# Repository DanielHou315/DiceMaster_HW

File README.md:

# DiceMaster HW

Hardware design files for the DiceMaster project, using KiCad.

## Board Status

The current production board is **PCB v1** (`PCB/DiceMaster_Router/`), finalized
for production on 2026-04-05 (commit `4ef69b5`, "finalized pcb v1 for prod").
Gerbers and the JLCPCB BOM under `PCB/DiceMaster_Router/gerbers/` are from this
run; the manufactured boards were received around mid-April 2026.

### Known issues (PCB v1 — unverified, to be handled later)

These issues were observed on the v1 boards but **not yet root-caused**:

1. **Some JST ports could not be soldered during manufacturing.** One or more of
   the JST GH SMD connectors (`J_A1`–`J_F1`, `J_BTN1`, `J_SWITCH1`, `J_FAN1`,
   `PiSugarPowerConnector1` — see `docs/runbooks/pcb-assembly.md` §4) could not
   be soldered on during assembly. Cause not yet determined (footprint/pad
   geometry vs. process).

2. **5V→3.3V converter does not work.** The onboard buck converter (IC1,
   TPS565201, SOT-23-6) did not produce a working 3.3 V rail after hand-soldering
   the part. It is **not yet known whether this is a design issue or a soldering
   issue** — this needs to be re-verified before the next production run. See the
   "No 3.3 V output" row in `docs/runbooks/pcb-assembly.md` §Troubleshooting and
   the converter subcircuit (IC1 / L1 / R_BOT1 / output caps) in the schematic.

> Status: both issues are **open and unverified**. Do not assume v1 boards have a
> working 3.3 V rail. Revisit during the next hardware bring-up / v2 design.

## KiCad MCP Server Setup

This project is configured with [kicad-mcp](https://github.com/lamaalrajih/kicad-mcp) to enable Claude Code to interact with KiCad projects directly.

### Prerequisites

- KiCad 9.0+ (installed at `/Applications/KiCad/KiCad.app`)
- Python 3.10+ and `uv`

### Installation

The MCP server is installed at `~/Applications/kicad-mcp`. To reinstall:

```bash
git clone https://github.com/lamaalrajih/kicad-mcp.git ~/Applications/kicad-mcp
cd ~/Applications/kicad-mcp
make install
cp .env.example .env
# Edit .env to set KICAD_SEARCH_PATHS to your project directory
```

### Usage

Start Claude Code from this directory — the `.mcp.json` file automatically connects the KiCad MCP server.

```bash
cd DiceMaster_HW
claude
```

Claude can then:

- **List projects** — discover KiCad projects in the configured search paths
- **Open projects** — launch KiCad with a specific project
- **Inspect schematics** — read components, nets, and symbols
- **Analyze PCBs** — view board properties, footprints, and design rules
- **Manage libraries** — search and retrieve KiCad symbols/footprints

### Configuration

- **`.mcp.json`** — MCP server config (points to the kicad-mcp installation)
- **`~/Applications/kicad-mcp/.env`** — KiCad paths and project search directories

To add more search paths, edit `~/Applications/kicad-mcp/.env`:

```
KICAD_SEARCH_PATHS=~/Code/DiceMaster/DiceMaster_HW,~/other/projects
```

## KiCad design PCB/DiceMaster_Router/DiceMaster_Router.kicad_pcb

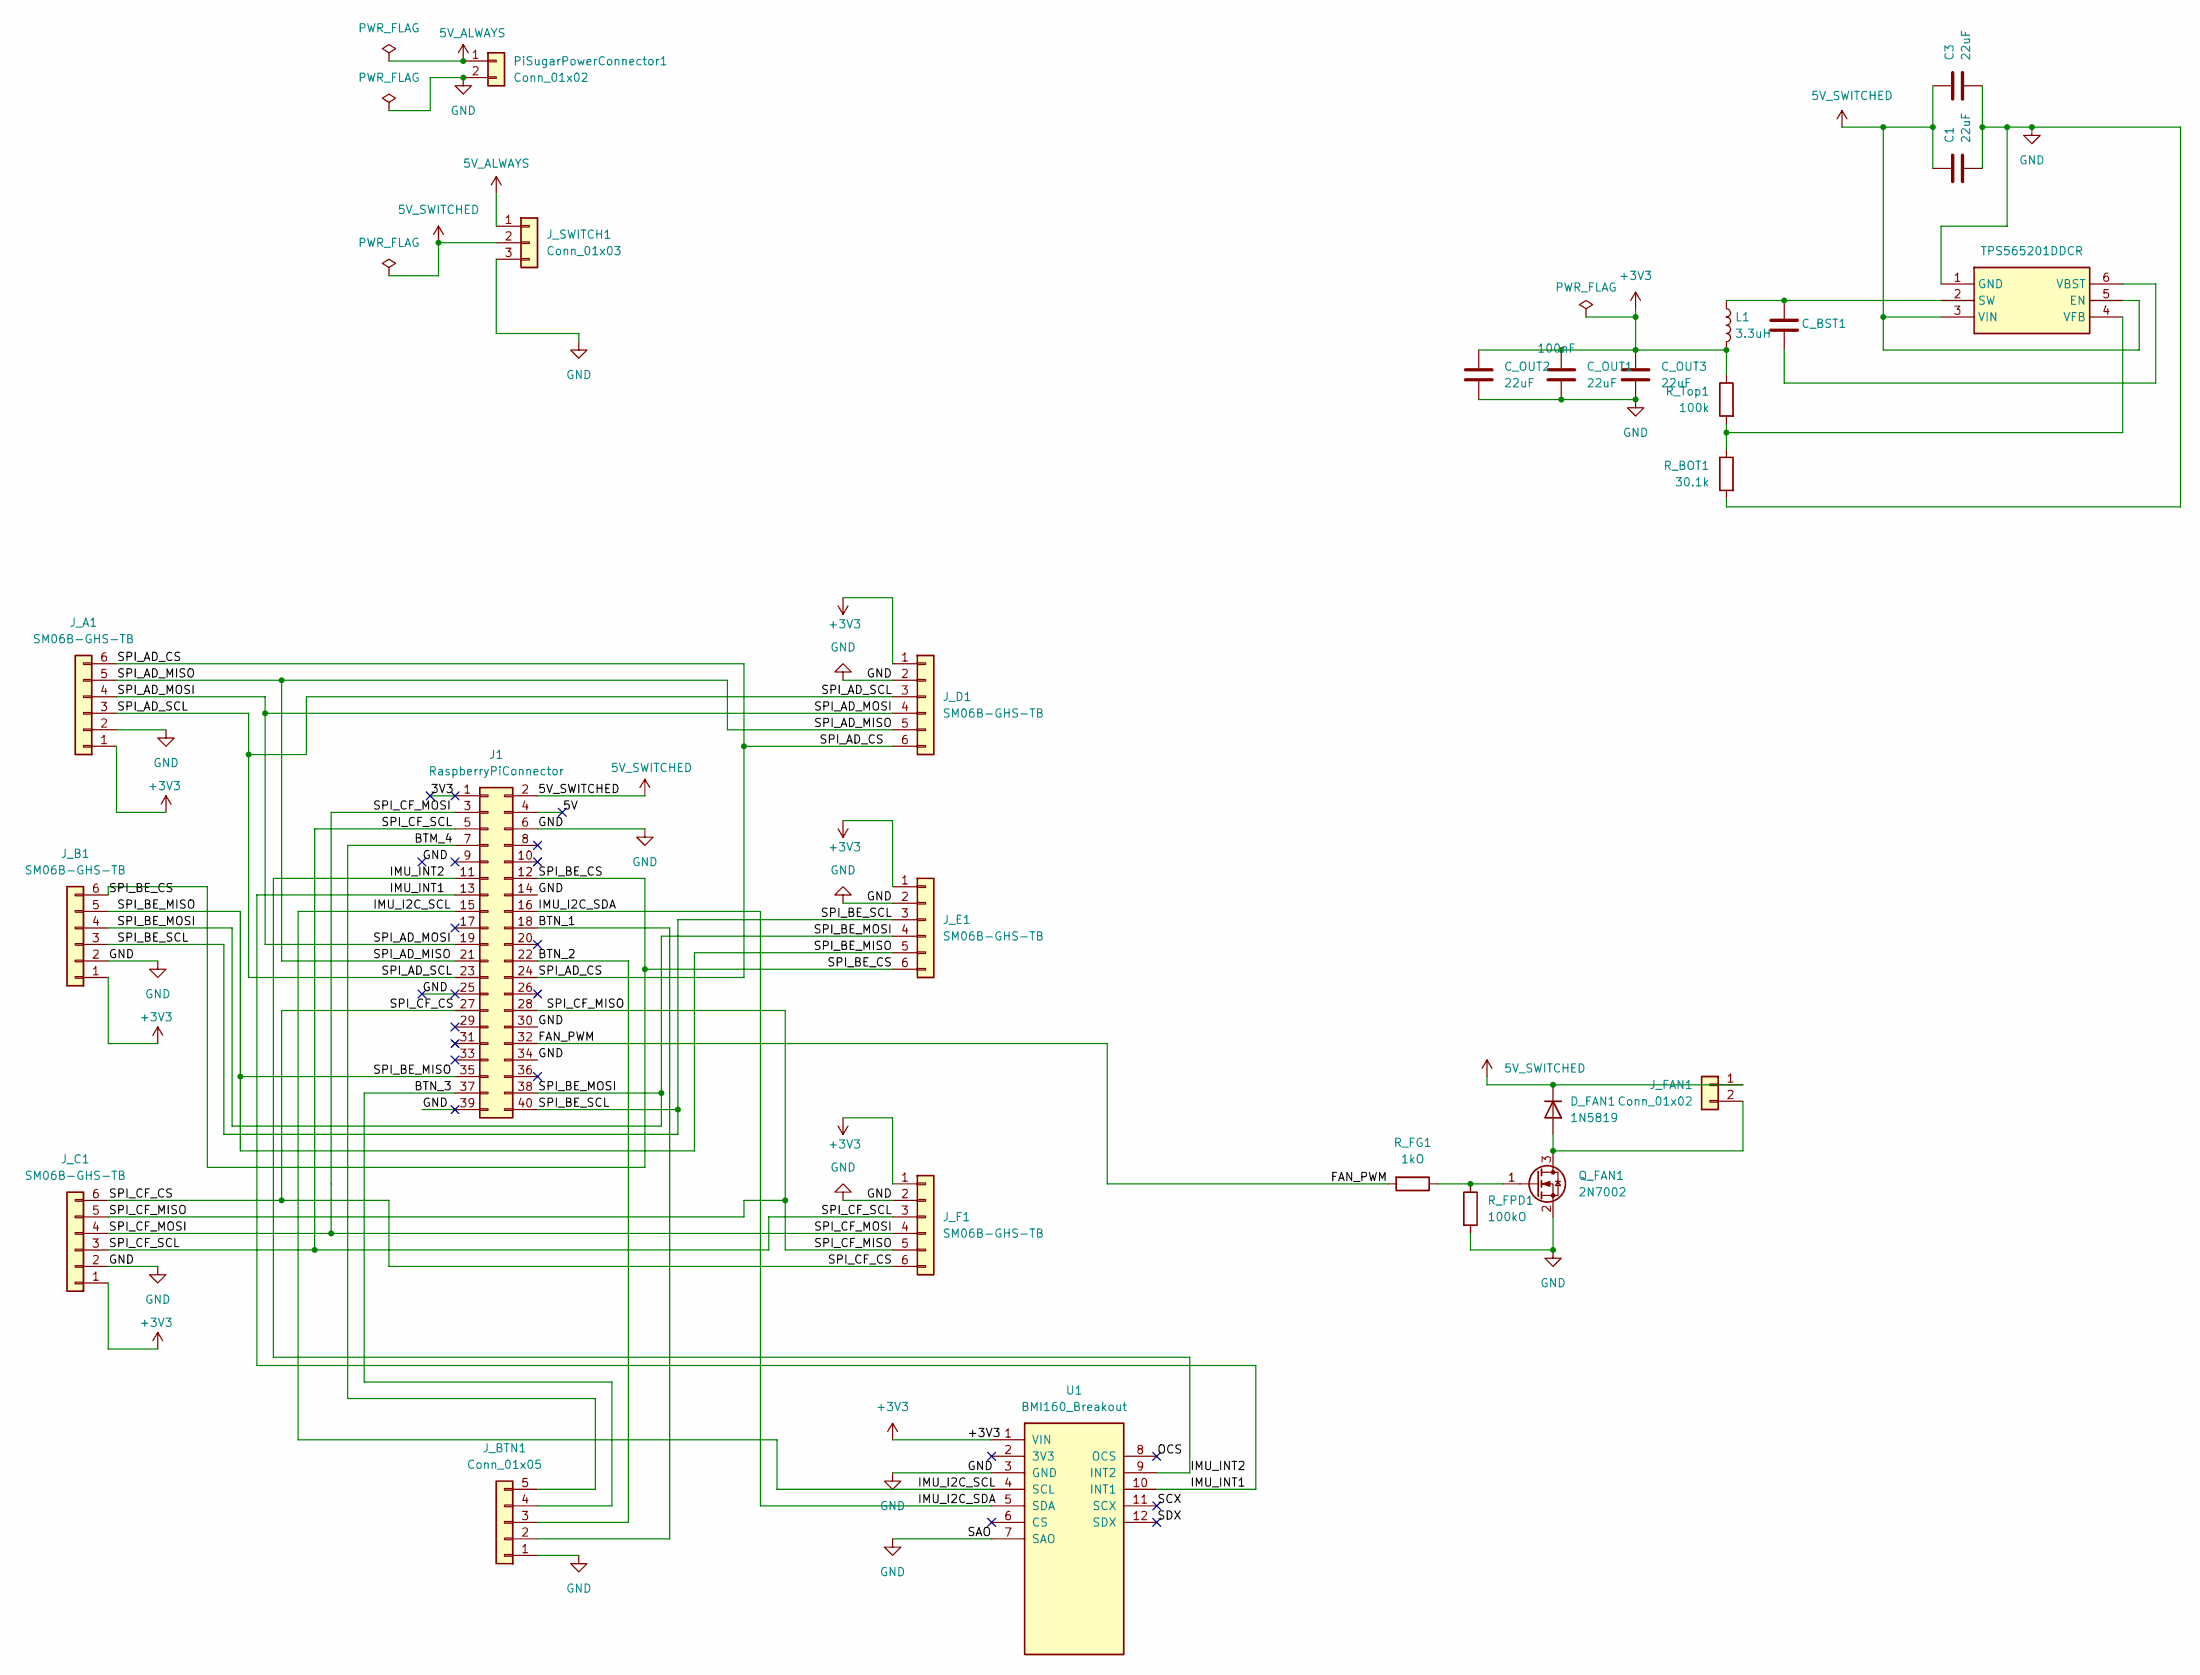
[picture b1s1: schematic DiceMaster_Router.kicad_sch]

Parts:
C1, C3: 22uF; C_0805_2012Metric
C_BST1: 100nF; C_0402_1005Metric
C_OUT1, C_OUT2, C_OUT3: 22uF; C_0805_2012Metric
D_FAN1: 1N5819; D_SOD-323
IC1: TPS565201DDCR; SOT95P280X110-6N; Manufacturer_Part_Number TPS565201DDCR; Mouser Part Number 595-TPS565201DDCR
J1: RaspberryPiConnector; PinSocket_2x20_P2.54mm_Vertical
J_A1: SM06B-GHS-TB; JST_GH_SM06B-GHS-TB_1x06-1MP_P1.25mm_Horizontal
J_B1: SM06B-GHS-TB; JST_GH_SM06B-GHS-TB_1x06-1MP_P1.25mm_Horizontal
J_BTN1: Conn_01x05; JST_GH_SM05B-GHS-TB_1x05-1MP_P1.25mm_Horizontal
J_C1: SM06B-GHS-TB; JST_GH_SM06B-GHS-TB_1x06-1MP_P1.25mm_Horizontal
J_D1: SM06B-GHS-TB; JST_GH_SM06B-GHS-TB_1x06-1MP_P1.25mm_Horizontal
J_E1: SM06B-GHS-TB; JST_GH_SM06B-GHS-TB_1x06-1MP_P1.25mm_Horizontal
J_F1: SM06B-GHS-TB; JST_GH_SM06B-GHS-TB_1x06-1MP_P1.25mm_Horizontal
J_FAN1: Conn_01x02; JST_GH_SM02B-GHS-TB_1x02-1MP_P1.25mm_Horizontal
J_SWITCH1: Conn_01x03; JST_GH_SM03B-GHS-TB_1x03-1MP_P1.25mm_Horizontal
L1: 3.3uH; L_Taiyo-Yuden_NR-50xx
PiSugarPowerConnector1: Conn_01x02; JST_GH_SM02B-GHS-TB_1x02-1MP_P1.25mm_Horizontal
Q_FAN1: 2N7002; SOT-23
R_BOT1: 30.1k; R_0402_1005Metric
R_FG1: 1kO; R_0402_1005Metric
R_FPD1: 100kO; R_0402_1005Metric
R_Top1: 100k; R_0402_1005Metric
U1: BMI160_Breakout

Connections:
5V_ALWAYS: J_SWITCH1.1, PiSugarPowerConnector1.1
5V_SWITCHED: C1.1, C3.1, D_FAN1.1 (K), IC1.3 (VIN), IC1.5 (EN), J1.2, J_FAN1.1, J_SWITCH1.2
+3V3: C_OUT1.1, C_OUT2.1, C_OUT3.1, J_A1.1, J_B1.1, J_C1.1, J_D1.1, J_E1.1, J_F1.1, L1.2, R_Top1.1, U1.1 (VIN)
/3V3: J1.1
/5V: J1.4
/BTM_4: J1.7, J_BTN1.5
/BTN_1: J1.18, J_BTN1.2
/BTN_2: J1.22, J_BTN1.3
/BTN_3: J1.37, J_BTN1.4
/FAN_PWM: J1.32, R_FG1.2
/IMU_I2C_SCL: J1.15, U1.4 (SCL)
/IMU_I2C_SDA: J1.16, U1.5 (SDA)
/IMU_INT1: J1.13, U1.10 (INT1)
/IMU_INT2: J1.11, U1.9 (INT2)
/OCS: U1.8 (OCS)
/SCX: U1.11 (SCX)
/SDX: U1.12 (SDX)
/SPI_AD_CS: J1.24, J_A1.6, J_D1.6
/SPI_AD_MISO: J1.21, J_A1.5, J_D1.5
/SPI_AD_MOSI: J1.19, J_A1.4, J_D1.4
/SPI_AD_SCL: J1.23, J_A1.3, J_D1.3
/SPI_BE_CS: J1.12, J_B1.6, J_E1.6
/SPI_BE_MISO: J1.35, J_B1.5, J_E1.5
/SPI_BE_MOSI: J1.38, J_B1.4, J_E1.4
/SPI_BE_SCL: J1.40, J_B1.3, J_E1.3
/SPI_CF_CS: J1.27, J_C1.6, J_F1.6
/SPI_CF_MISO: J1.28, J_C1.5, J_F1.5
/SPI_CF_MOSI: J1.3, J_C1.4, J_F1.4
/SPI_CF_SCL: J1.5, J_C1.3, J_F1.3
GND: C1.2, C3.2, C_OUT1.2, C_OUT2.2, C_OUT3.2, IC1.1 (GND), J1.6, J1.14, J1.25, J1.30, J1.34, J1.39, J_A1.2, J_B1.2, J_BTN1.1, J_C1.2, J_D1.2, J_E1.2, J_F1.2, J_SWITCH1.3, PiSugarPowerConnector1.2, Q_FAN1.2 (S), R_BOT1.2, R_FPD1.2, U1.3 (GND), U1.7 (SAO)
unnamed: D_FAN1.2 (A), J_FAN1.2, Q_FAN1.3 (D)
unnamed: C_BST1.1, IC1.2 (SW), L1.1
unnamed: C_BST1.2, IC1.6 (VBST)
unnamed: IC1.4 (VFB), R_BOT1.1, R_Top1.2
unnamed: Q_FAN1.1 (G), R_FG1.1, R_FPD1.1

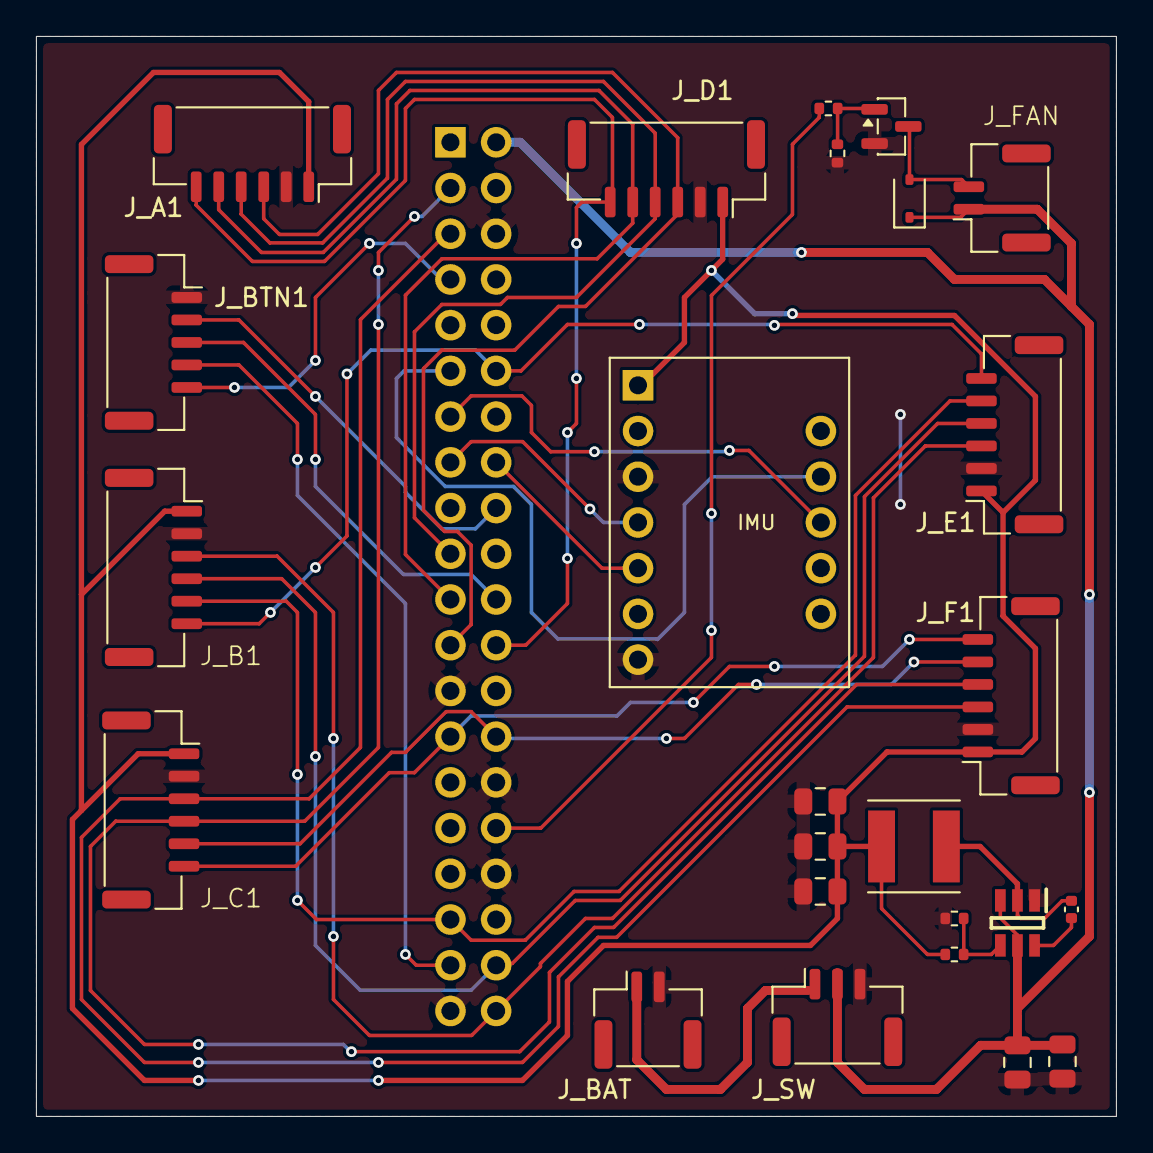
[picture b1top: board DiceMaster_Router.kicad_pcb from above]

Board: 2 copper layers, 60.0 x 60.0 mm, 26 parts (1 on the bottom side), 30 nets.

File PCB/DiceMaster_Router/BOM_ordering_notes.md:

# DiceMaster Router - BOM & Ordering Notes

## JLCPCB SMD Assembly Parts

### Resistors (0402, 1%)
| Ref | Value | Package | Notes |
|-----|-------|---------|-------|
| R_FG1 | 1kΩ | 0402 | MOSFET gate resistor |
| R_FPD1 | 100kΩ | 0402 | MOSFET gate pull-down |
| R_Top1 | 100kΩ | 0402 | TPS565201 feedback divider top |
| R_BOT1 | 30.1kΩ | 0402 | TPS565201 feedback divider bottom. **Must be 1% tolerance** — sets 3.3V output voltage |

### Capacitors (0402 / 0805)
| Ref | Value | Package | Notes |
|-----|-------|---------|-------|
| C_BST1 | 100nF | 0402 | TPS565201 bootstrap cap |
| C1 | 22µF | 0805 | TPS565201 input cap. **Must be ≥10V rated.** e.g., Samsung CL21A226MAQNNNE |
| C3 | 22µF | 0805 | TPS565201 input cap. Same spec as C1 |
| C_OUT1 | 22µF | 0805 | TPS565201 output cap. ≥10V rated |
| C_OUT2 | 22µF | 0805 | TPS565201 output cap. ≥10V rated |
| C_OUT3 | 22µF | 0805 | TPS565201 output cap. ≥10V rated |

**WARNING:** 0805 22µF ceramic caps at 6.3V rating have severe DC bias derating — at 5V they may only provide ~10µF effective capacitance. Always pick **≥10V rated** parts to maintain full capacitance at operating voltage.

### Inductor
| Ref | Value | Package | Notes |
|-----|-------|---------|-------|
| L1 | 3.3µH | 5x5mm (NR-50xx) | Power inductor for TPS565201. **Must be rated ≥3A saturation current.** Search JLCPCB for "3.3uH 5040" or "3.3uH 5020". e.g., Sunlord SWPA5040S3R3NT |

### Semiconductor
| Ref | Value | Package | Notes |
|-----|-------|---------|-------|
| IC1 | TPS565201DDCR | SOT-23-6 (SOT95P280X110-6N) | 5V→3.3V buck converter |
| Q_FAN1 | 2N7002 | SOT-23 | N-channel MOSFET, fan driver. 115mA max continuous |
| D_FAN1 | 1N5819 | SOD-323 | Schottky flyback diode. SOD-323 equivalent: 1N5819HW or B5819W |

### Fan Current Budget
- Fan: WINSINN 30mm 5V Blower (0.09A / 0.5W)
- Q_FAN (2N7002) rated 115mA continuous
- Margin: 26mA (23%) — acceptable for this fan, but do NOT substitute a larger fan without upgrading the MOSFET (e.g., IRLML6344 for >1A fans)

## Hand-Soldered Connectors

| Ref | Part | Notes |
|-----|------|-------|
| J1 | 2x20 pin socket header, 2.54mm | Raspberry Pi 40-pin female header |
| J_A1–J_F1 | SM06B-GHS-TB | JST GH 6-pin SMD horizontal |
| J_BTN1 | SM05B-GHS-TB | JST GH 5-pin SMD horizontal |
| J_SWITCH1 | SM03B-GHS-TB | JST GH 3-pin SMD horizontal |
| J_FAN1 | SM02B-GHS-TB | JST GH 2-pin SMD horizontal |
| PiSugarPowerConnector1 | SM02B-GHS-TB | JST GH 2-pin SMD horizontal |

## IMU Breakout (separate board, plugs in)

| Part | Notes |
|------|-------|
| GY-BMI160 | 18.3mm × 13.3mm breakout board. Mounts via pin headers into U1 footprint (7+5 pin, 10.16mm row spacing, 2.54mm pitch) |

## PCB Specs for JLCPCB Order
- Max board size: 60mm × 60mm
- Layers: 2 (or 4 if routing is tight)
- Copper weight: 1oz standard
- Surface finish: HASL or LeadFree HASL

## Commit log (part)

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2026-03-08 Add CLAUDE.md and .claude/ to gitignore
2026-04-05 rough schematic added
2026-04-05 Finished PCB v1
2026-04-05 finalized pcb v1 for prod
